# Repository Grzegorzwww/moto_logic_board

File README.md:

# moto_logic_board
moto_logic_board

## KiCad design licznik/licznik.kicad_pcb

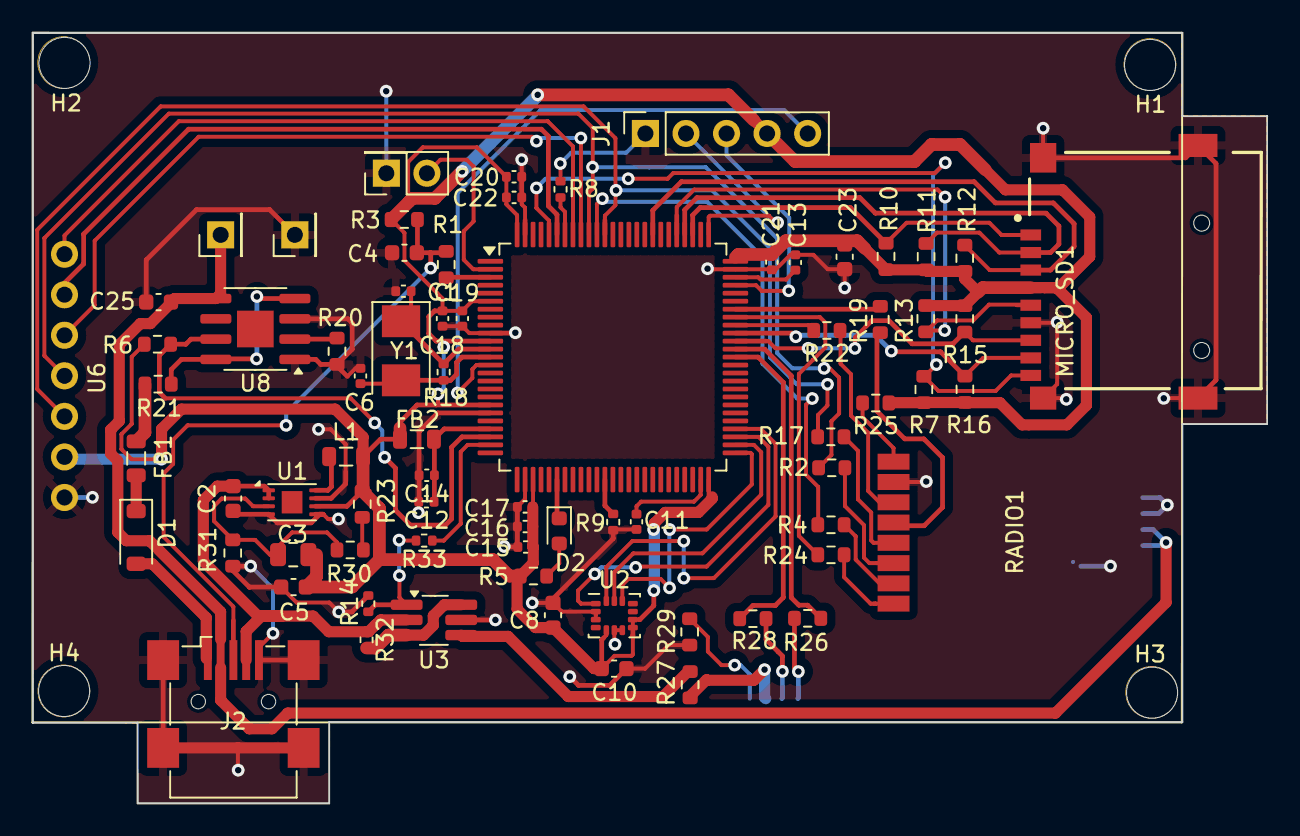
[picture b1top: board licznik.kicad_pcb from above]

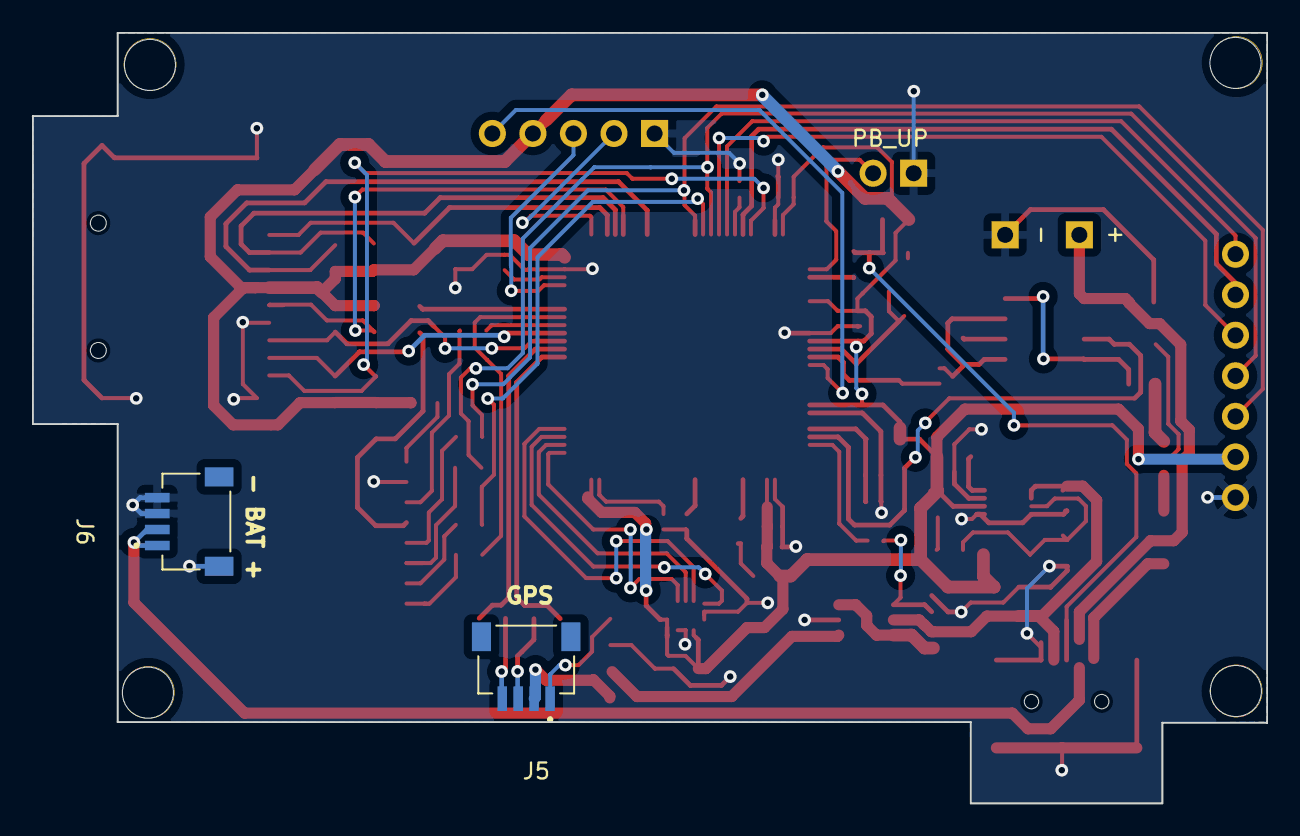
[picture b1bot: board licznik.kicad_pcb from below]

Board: 2 copper layers, 77.3 x 48.3 mm, 80 parts (2 on the bottom side), 65 nets.

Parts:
+: BAT+; PinHeader_1x01_P2.54mm_Vertical
-: BAT-; PinHeader_1x01_P2.54mm_Vertical
C1, C6: 12pF; C_0402_1005Metric
C2, C5, C25: 10uF; C_0603_1608Metric
C3: 47pF; C_0805_2012Metric
C4, C8, C10, C23: 100nF; C_0603_1608Metric
C11, C13: 2.2uF; C_0402_1005Metric
C12, C16, C17, C18, C19, C20, C21, C22: 100nF; C_0402_1005Metric
C14: 10nF; C_0402_1005Metric
C15: 10uF; C_0402_1005Metric
CPU1: STM32F407VETx; LQFP-100_14x14mm_P0.5mm
D1: B5819W; D_SOD-123
D2: LED; LED_0603_1608Metric
FB1, FB2: 100@100Mhz; L_0805_2012Metric
H1, H2, H3, H4: MountingHole_Pad; MountingHole_3.2mm_M3
J1: Conn_01x05_Female; PinSocket_1x05_P2.54mm_Vertical
J2: USB_B_Mini; USB_Mini-B_Wuerth_65100516121_Horizontal
J5, J6: PRT-14417; SPARKFUN_PRT-14417
L1: 10uH; L_0805_2012Metric
MICRO_SD1: TF-01A
PB_UP: SW_Push; PinSocket_2x01_P2.54mm_Vertical
R1: 50K; R_0603_1608Metric
R2, R4, R17, R19, R22, R24, R25, R26, R27, R28, R29: 0R; R_0603_1608Metric
R3, R6, R7, R10, R11, R12, R13, R15, R16: 10K; R_0603_1608Metric
R5: 510R; R_0603_1608Metric
R8, R9, R33: 10K; R_0402_1005Metric
R14, R32: 100K; R_0402_1005Metric
R18: 1M; R_0402_1005Metric
R20: 2K; R_0603_1608Metric
R21: 0.1R; R_0603_1608Metric
R23: 510K; R_0603_1608Metric
R30: 120K; R_0603_1608Metric
R31: 200K; R_0603_1608Metric
RADIO1: NRF24L01_Breakout; NRF24L01-SMD_mini
U1: MCP1601-I_MS; TDFN-8-1EP_3x2mm_P0.5mm_EP1.3x1.4mm
U2: LSM6DS3; LGA-14_3x2.5mm_P0.5mm_LayoutBorder3x4y
U3: TSOT-23-6_HandSoldering
U6: oled; ol1
U8: TP4056; HSOP-8-1EP_3.9x4.9mm_P1.27mm_EP2.3x2.3mm
Y1: Crystal; Crystal_SMD_5032-2Pin_5.0x3.2mm

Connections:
+3.3VA: C12.1, C14.1, CPU1.22 (VDDA), FB2.1
+3V3: C3.1, C5.1, C8.1, C10.2, C15.1, C16.1, C17.1, C18.1, C19.1, C20.1, C21.1, C22.1, C23.1, CPU1.6 (VBAT), CPU1.11 (VDD), CPU1.19 (VDD), CPU1.28 (VDD), CPU1.50 (VDD), CPU1.75 (VDD), CPU1.100 (VDD), FB2.2, J1.4, L1.2, MICRO_SD1.4 (VDD), R3.2, R5.2, R6.2, R7.2, R10.2, R11.2, R12.2, R13.2, R15.2, R16.2, R23.2, R25.1, U1.6 (VOUT), U2.5 (VDDIO), U2.8 (VDD), U2.9 (INT2), U6.2 (VCC)
+5V: FB1.1, R21.1
CHRG_SIGNAL: CPU1.23 (PA0), R6.1, U8.7 (~CHRG)
GND: -.1, C1.2, C2.2, C4.2, C5.2, C6.2, C8.2, C10.1, C11.2, C12.2, C13.2, C14.2, C15.2, C16.2, C17.2, C18.2, C19.2, C20.2, C21.2, C22.2, C23.2, C25.2, CPU1.10 (VSS), CPU1.20 (VSSA), CPU1.27 (VSS), CPU1.74 (VSS), CPU1.99 (VSS), J1.1, J2.5 (GND), J2.6 (Shield), J6.3, J6.4, MICRO_SD1.6 (VSS), MICRO_SD1.MP1 (SHIELD), MICRO_SD1.MP2 (SHIELD), MICRO_SD1.MP3 (SHIELD), MICRO_SD1.MP4 (SHIELD), PB_UP.1, R8.1, R9.1, R14.2, R20.2, R29.2, R31.1, RADIO1.1 (GND), U1.4 (AGND), U1.5 (SYNC/PWM), U1.7 (PGND), U2.2 (SDX), U2.3 (SCX), U2.6 (GND), U2.7 (GND), U3.5, U6.1 (GND), U8.1 (TEMP), U8.3 (GND)
GPS_ON_OFF: CPU1.24 (PA1), R33.1
GPS_UART_RX: CPU1.64 (PC7), R26.2
GPS_UART_TX: CPU1.63 (PC6), R28.2
GYRO_CS: CPU1.51 (PB12), U2.12 (CS)
GYRO_MISO: CPU1.53 (PB14), U2.1 (SDO/SA0)
GYRO_MOSI: CPU1.54 (PB15), U2.14 (SDA)
GYRO_SCK: CPU1.52 (PB13), U2.13 (SCL)
HSE_IN: C1.1, CPU1.12 (PH0), R18.2, Y1.1
HSE_OUT: C6.1, CPU1.13 (PH1), R18.1, Y1.2
LED_1: CPU1.31 (PA6), D2.1 (K)
NRST: CPU1.14 (NRST), J1.5
unnamed: CPU1.94 (BOOT0), R8.2
unnamed: CPU1.37 (PB2), R9.2
unnamed: C11.1, CPU1.49 (VCAP_1)
unnamed: C13.1, CPU1.73 (VCAP_2)
unnamed: D1.2 (A), J2.1 (VBUS)
unnamed: D1.1 (K), FB1.2
unnamed: D2.2 (A), R5.1
unnamed: J5.1, R29.1
unnamed: J5.2, R27.1
unnamed: J5.3, R28.1
unnamed: J5.4, R26.1
unnamed: R14.1, R33.2, U3.1
unnamed: R23.1, R30.2
unnamed: R27.2, U3.4
unnamed: R32.2, U3.3, U3.6
unnamed: R22.1, RADIO1.3 (CE)
unnamed: R24.1, RADIO1.8 (IRQ)
unnamed: R4.1, RADIO1.7 (MISO)
unnamed: R2.1, RADIO1.6 (MOSI)
unnamed: R17.1, RADIO1.5 (SCK)
unnamed: R25.2, RADIO1.2 (VCC)
unnamed: R19.1, RADIO1.4 (~CSN)
unnamed: C3.2, R30.1, R31.2, U1.3 (FB)
unnamed: L1.1, U1.8 (LX)
unnamed: R21.2, U8.4 (VCC), U8.8 (CE)
unnamed: R20.1, U8.2 (PROG)
OLED_CS: CPU1.93 (PB7), U6.7 (CS)
OLED_DC: CPU1.95 (PB8), U6.6 (DC)
OLED_MISO: CPU1.90 (PB4), R4.2
OLED_MOSI: CPU1.91 (PB5), R2.2, U6.4 (SDA)
OLED_RST: CPU1.92 (PB6), U6.5 (RES)
OLED_SCK: CPU1.89 (PB3), R17.2, U6.3 (SCL)
PB_DOWN: CPU1.3 (PE4), R1.1
PB_UP: CPU1.2 (PE3), PB_UP.2
PUSH_DOWN_IN: C4.1, J2.3 (D+), R1.2, R3.1
SDIO_CMD: CPU1.83 (PD2), MICRO_SD1.3 (CMD), R12.1
SDIO_D0: CPU1.65 (PC8), MICRO_SD1.7 (DAT0), R15.1
SDIO_D1: CPU1.66 (PC9), MICRO_SD1.8 (DAT1), R16.1
SDIO_D2: CPU1.78 (PC10), MICRO_SD1.1 (DAT2), R10.1
SDIO_D3: CPU1.79 (PC11), MICRO_SD1.2 (CD/DAT3), R11.1
SDIO_INSERT_CARD: CPU1.96 (PB9), MICRO_SD1.CD1 (CD), R7.1
SDIO_SCK: CPU1.80 (PC12), MICRO_SD1.5 (CLK), R13.1
SWDCLK: CPU1.76 (PA14), J1.2
SWDIO: CPU1.72 (PA13), J1.3
SW_IN: +.1, C25.1, J2.2 (D-), J6.1, J6.2, U8.5 (BAT)
SW_OUT: C2.1, J2.4 (ID), R32.1, U1.1 (VIN), U1.2 (~SHDN), U3.2
nRF24_CE: CPU1.67 (PA8), R22.2
nRF24_CNS: CPU1.69 (PA10), R19.2
nRF24_IRQ: CPU1.68 (PA9), R24.2

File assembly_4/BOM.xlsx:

Designator | Quantity | Value | Footprint | LCSC Part Number | WHAT
C17,C20,C18,C19,C22,C12,C21,C16 | 8 | 100nF |  | C432917
R12,R15,R13,R7,R16,R6,R11,R10,R3 | 9 | 10K |  | C25804
PB_UP | 1 | - |  |  | NOT MOUNT
C5,C2,C25 | 3 | 10uF |  | C19702
C6,C1 | 2 | 12pF |  | C1547
R26,R2,R28,R4,R14,R29,R24,R19,R17,R22,R25,R27 | 12 | 0R |  | C21189
H1,H4,H2,H3 | 4 | - |  |  | NOT MOUNT
C4,C10,C8,C23 | 4 | 100nF |  | C14663
D2 | 1 | LED |  | C2286
R20 | 1 | 2K |  | C22975
C13,C11 | 2 | 2.2uF |  | C12530
J2 | 1 | USB |  |  | NOT MOUNT
R1 | 1 | 51K |  | C23196
MICRO_SD1 |  | - |  |  | NOT MOUNT
C14 | 1 | 10nF |  | C15195
U2 | 1 | LSM6DS3TR |  | C95230
R5 | 1 | 510R |  | C23193
FB1,FB2 | 2 | 100@100Mhz |  | C1017
C15 | 1 | 10uF |  | C15525
L1 | 1 | 10uH |  | C1046
D1 | 1 | B5819W |  | C8598
J1 | 1 | - |  |  | NOT MOUNT
R30 | 1 | 120K |  | C25808
R8,R9 | 2 | 10K |  | C25744
J4 | 1 | - |  |  | NOT MOUNT
Y1 | 1 | Crytal |  | C115962
R23 | 1 |  |  | C23192
R18 | 1 |  |  | C26083
R21 | 1 |  |  | C22936
J3 | 1 | - |  |  | NOT MOUNT
RADIO1 | 1 |  |  |  | NOT MOUNT
U8 | 1 | TP4056 |  |  | NOT MOUNT
CPU1 | 1 | STM32 |  | C28730
U1 | 1 | MCP |  |  | NOT MOUNT
R31 | 1 | 200K |  | C25811
U6 | 1 | - |  |  | NOT MOUNT
C3 | 1 | - |  | C96123
J6 | 1 | - |  |  | NOT MOUNT
J5 | 1 | - |  |  | NOT MOUNT

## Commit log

2024-05-26 hardware_2
2024-06-13 ulepszony pcb
2024-06-14 add nRF
2024-07-11 przed poprawkami
2024-07-25 proukcja v5
2024-09-10 produkcja v6
